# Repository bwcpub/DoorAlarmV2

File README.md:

# DoorAlarmV2

## A newer, hopefully better, version of the Door Alarm board.

**(C) 2022 Ben Cantrick. These files are distributed under a Creative Commons Attribution-ShareAlike license, see LICENSE_CCBYSA40.TXT.**

A newer, hopefully better, version of the Door Alarm board. Now fully compliant with the "just use a 555 timer" meme!

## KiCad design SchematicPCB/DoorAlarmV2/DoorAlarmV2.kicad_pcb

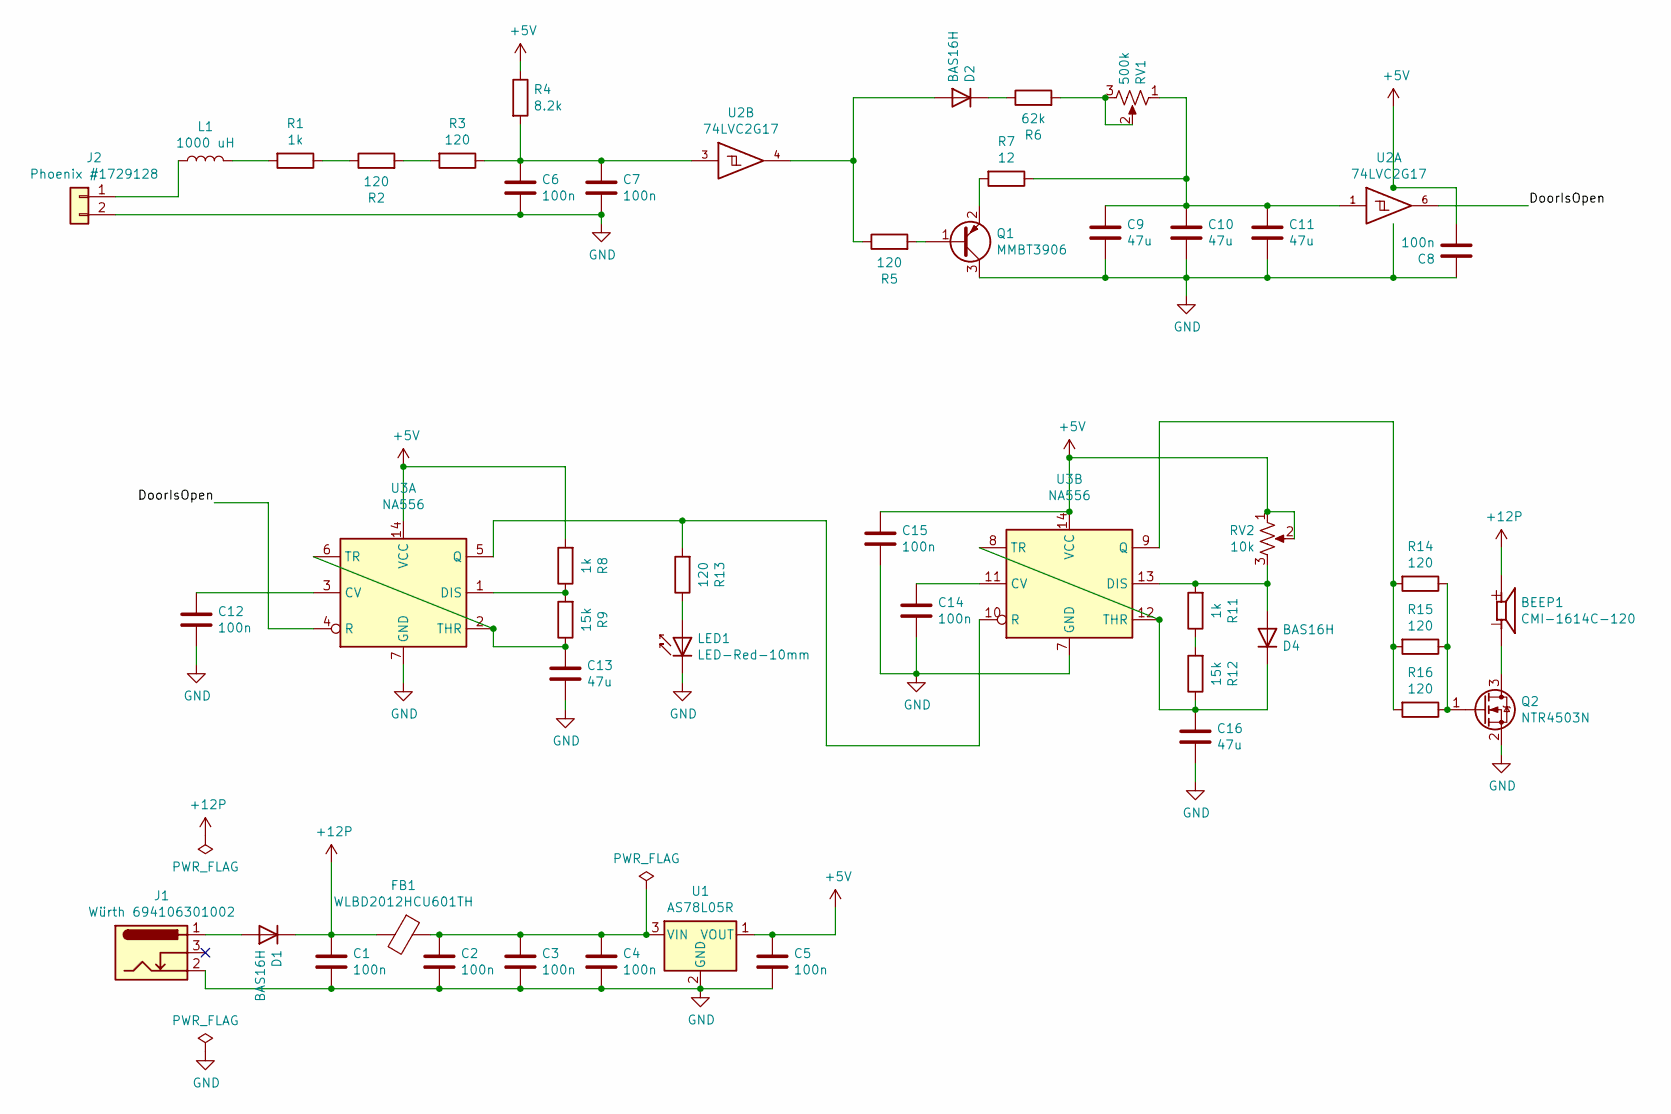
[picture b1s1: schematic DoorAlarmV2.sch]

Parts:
BEEP1: CMI-1614C-120; CUI_CMI-1614C-120
C1, C2, C3, C4, C5, C6, C7, C8, C12, C14, C15: 100n; C_0805_2012Metric
C9, C10, C11, C13, C16: 47u; R_1210_3225Metric
D1, D2, D4: BAS16H; D_SOD-323
FB1: WLBD2012HCU601TH; L_0805_2012Metric
J1: Würth 694106301002; BarrelJack_Wuerth_6941xx301002
J2: Phoenix #1729128; TerminalBlock_Phoenix_MKDS-1,5-2-5.08_1x02_P5.08mm_Horizont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
L1: 1000 uH; L_1210_3225Metric
LED1: LED-Red-10mm; LED_D10.0mm
Q1: MMBT3906; SOT-23
Q2: NTR4503N; SOT-23
R1, R8, R11: 1k; R_0805_2012Metric
R2, R3, R5, R13, R14, R15, R16: 120; R_0805_2012Metric
R4: 8.2k; R_0805_2012Metric
R6: 62k; R_0805_2012Metric
R7: 12; R_0805_2012Metric
R9, R12: 15k; R_0805_2012Metric
RV1: 500k; Potentiometer_Bourns_TC33X_Vertical
RV2: 10k; Potentiometer_Bourns_TC33X_Vertical
U1: AS78L05R; SOT-89-3
U2: 74LVC2G17; SOT-23-6
U3: NA556; SSOP-14_5.3x6.2mm_P0.65mm

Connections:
+5V: C5.1, C8.2, C15.1, R4.1, R8.2, RV2.1, RV2.2, U1.1 (VOUT), U2.5 (VCC), U3.14 (VCC)
+12P: BEEP1.P, C1.1, D1.1 (K), FB1.2
/DoorIsOpen: U2.6, U3.4 (R)
GND: C1.2, C2.2, C3.2, C4.2, C5.2, C6.2, C7.2, C8.1, C9.2, C10.2, C11.2, C12.2, C13.2, C14.2, C15.2, C16.2, J1.2, J2.2, LED1.1 (K), Q1.3 (C), Q2.2 (S), U1.2 (GND), U2.2 (GND), U3.7 (GND)
unnamed: BEEP1.N, Q2.3 (D)
unnamed: C2.1, C3.1, C4.1, FB1.1, U1.3 (VIN)
unnamed: C6.1, C7.1, R3.1, R4.2, U2.3
unnamed: C9.1, C10.1, C11.1, R7.1, RV1.1, U2.1
unnamed: C12.1, U3.3 (CV)
unnamed: C13.1, R9.1, U3.2 (THR), U3.6 (TR)
unnamed: C14.1, U3.11 (CV)
unnamed: C16.1, D4.1 (K), R12.1, U3.8 (TR), U3.12 (THR)
unnamed: D1.2 (A), J1.1
unnamed: D2.1 (K), R6.1
unnamed: D2.2 (A), R5.1, U2.4
unnamed: D4.2 (A), R11.2, RV2.3, U3.13 (DIS)
unnamed: J2.1, L1.1
unnamed: L1.2, R1.2
unnamed: LED1.2 (A), R13.1
unnamed: Q1.1 (B), R5.2
unnamed: Q1.2 (E), R7.2
unnamed: Q2.1 (G), R14.1, R15.1, R16.1
unnamed: R1.1, R2.1
unnamed: R2.2, R3.2
unnamed: R6.2, RV1.2, RV1.3
unnamed: R8.1, R9.2, U3.1 (DIS)
unnamed: R11.1, R12.2
unnamed: R13.2, U3.5 (Q), U3.10 (R)
unnamed: R14.2, R15.2, R16.2, U3.9 (Q)

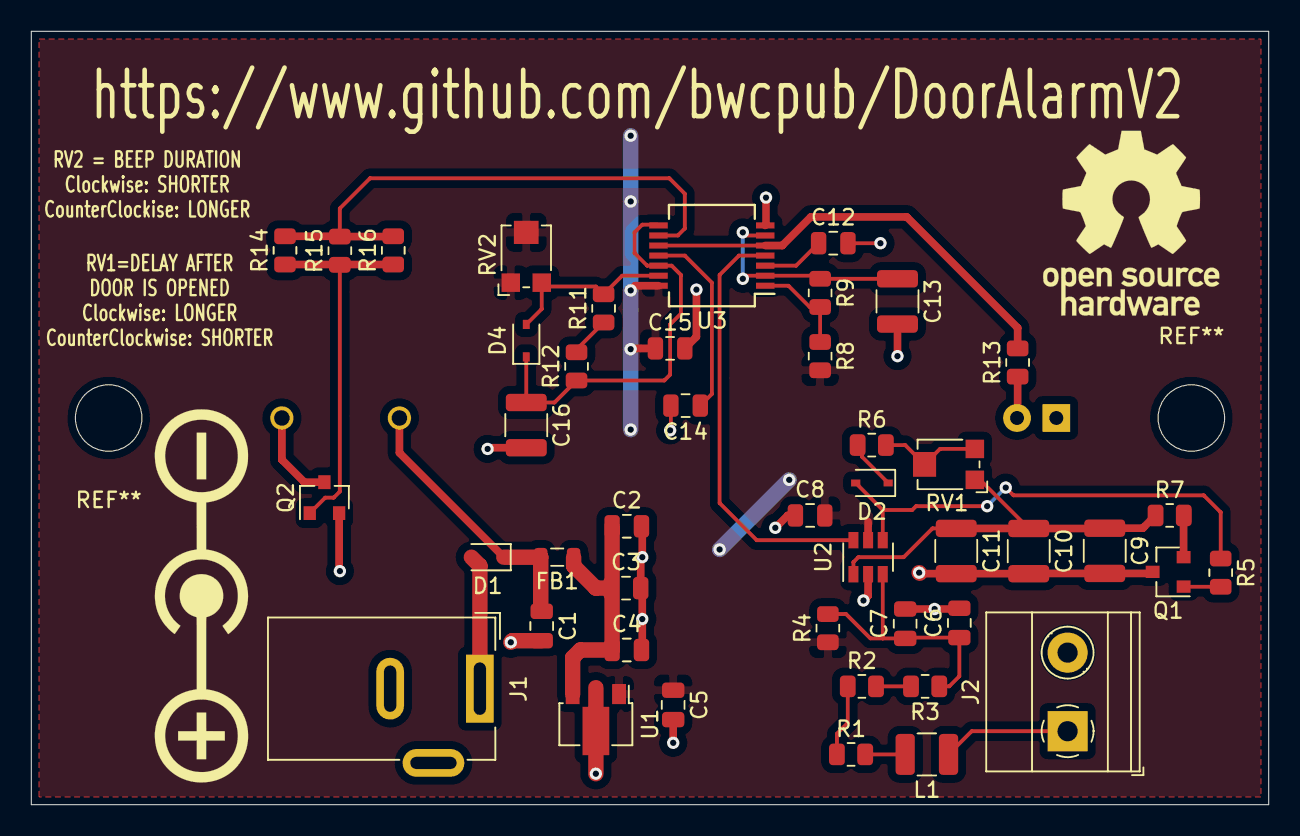
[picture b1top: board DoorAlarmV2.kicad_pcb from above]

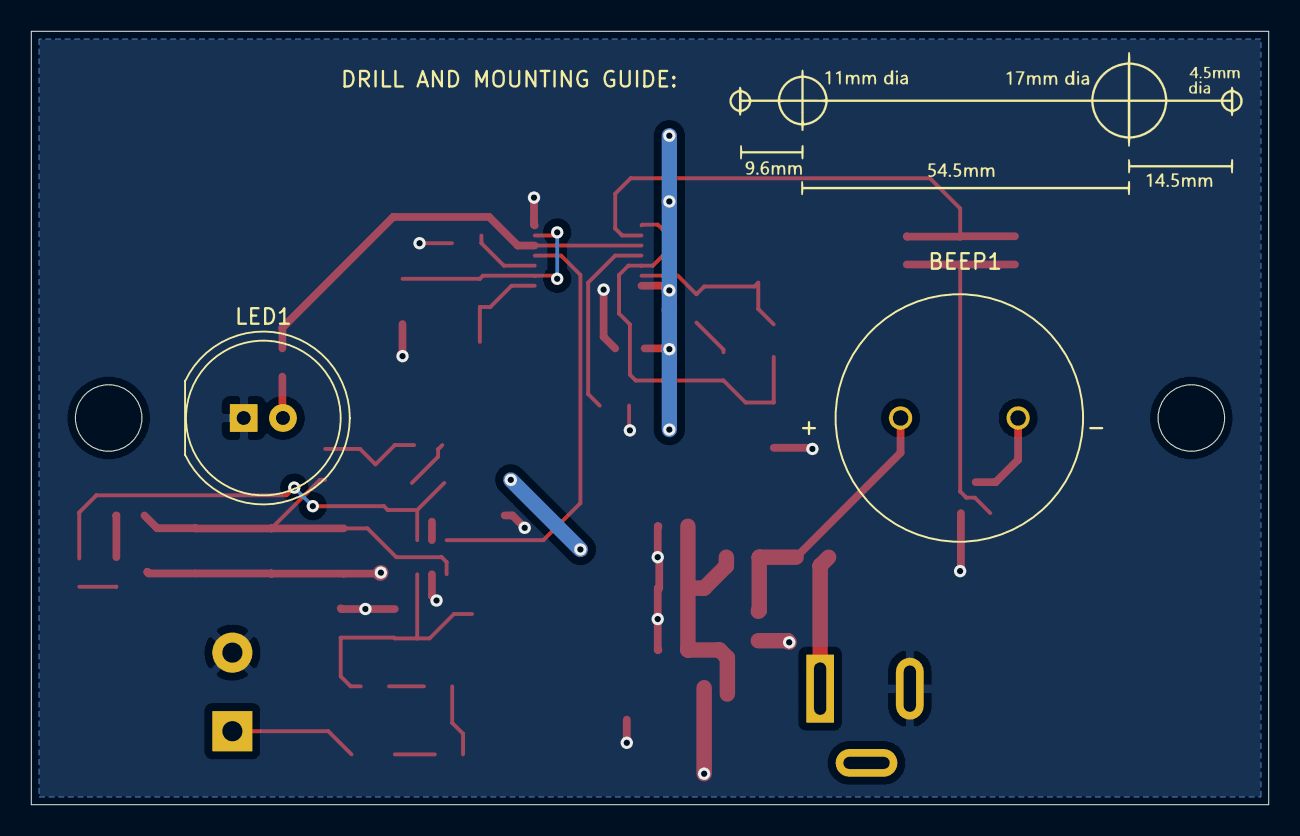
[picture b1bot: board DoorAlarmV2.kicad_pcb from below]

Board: 2 copper layers, 80.0 x 50.0 mm, 47 parts (2 on the bottom side), 29 nets.

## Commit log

2022-12-06 Added brief project description
2022-12-07 Added screenshot.
2022-12-07 Github's suggested quotations marks are a disaster. Fixed.
